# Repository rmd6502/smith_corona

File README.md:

smith_corona
============

Driver for Smith Corona typewriter

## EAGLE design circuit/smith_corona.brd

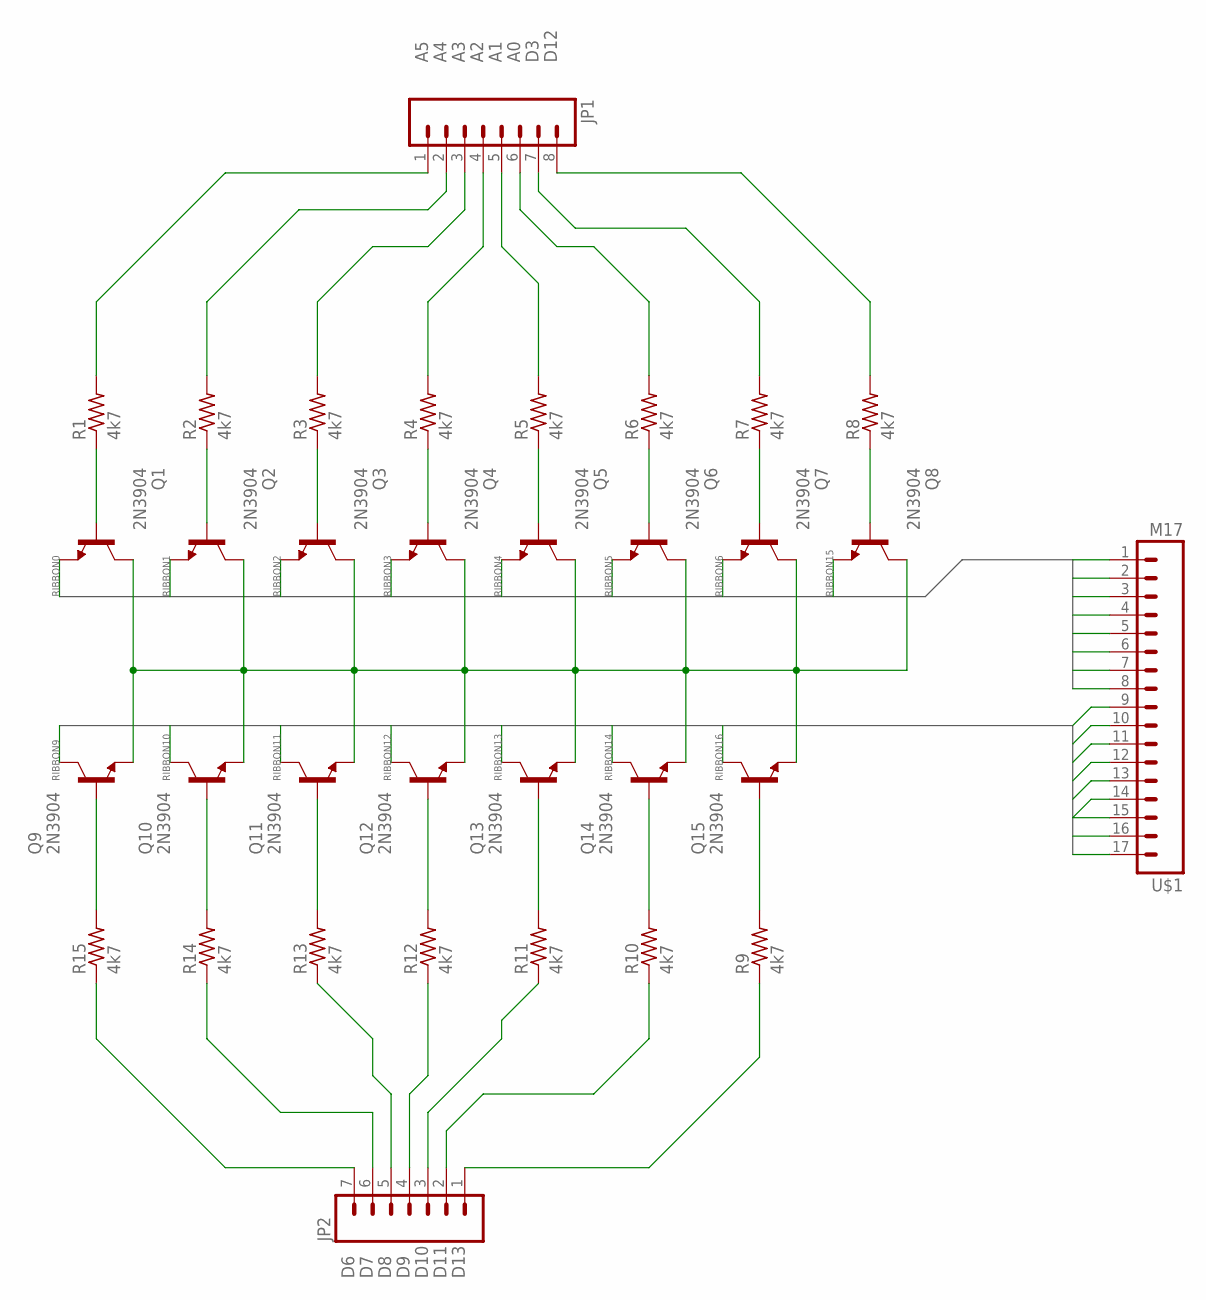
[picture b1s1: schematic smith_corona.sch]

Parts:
JP1: M08LONGPADS; 1X08_LONGPADS
JP2: M07LONGPADS; 1X07_LONGPADS
Q1, Q2, Q3, Q4, Q5, Q6, Q7, Q8, Q9, Q10, Q11, Q12, Q13, Q14, Q15: 2N3904; TO92
R1, R2, R3, R4, R5, R6, R7, R8, R9, R10, R11, R12, R13, R14, R15: 4k7; 0207/10
U$1: M17; 1X17

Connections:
A0: JP1.6, R6.2
A1: JP1.5, R5.2
A2: JP1.4, R4.2
A3: JP1.3, R3.2
A4: JP1.2, R2.2
A5: JP1.1, R1.2
D3: JP1.7, R7.2
D6: JP2.7, R15.1
D7: JP2.6, R14.1
D8: JP2.5, R13.1
D9: JP2.4, R12.1
D10: JP2.3, R11.1
D11: JP2.2, R10.1
D12: JP1.8, R8.2
D13: JP2.1, R9.1
unnamed: Q1.2 (B), R1.1
unnamed: Q2.2 (B), R2.1
unnamed: Q3.2 (B), R3.1
unnamed: Q4.2 (B), R4.1
unnamed: Q5.2 (B), R5.1
unnamed: Q6.2 (B), R6.1
unnamed: Q7.2 (B), R7.1
unnamed: Q8.2 (B), R8.1
unnamed: Q15.2 (B), R9.2
unnamed: Q14.2 (B), R10.2
unnamed: Q13.2 (B), R11.2
unnamed: Q12.2 (B), R12.2
unnamed: Q11.2 (B), R13.2
unnamed: Q10.2 (B), R14.2
unnamed: Q9.2 (B), R15.2
unnamed: Q1.1 (C), Q2.1 (C), Q3.1 (C), Q4.1 (C), Q5.1 (C), Q6.1 (C), Q7.1 (C), Q8.1 (C), Q9.3 (E), Q10.3 (E), Q11.3 (E), Q12.3 (E), Q13.3 (E), Q14.3 (E), Q15.3 (E)
RIBBON0: Q1.3 (E), U$1.1
RIBBON1: Q2.3 (E), U$1.2
RIBBON2: Q3.3 (E), U$1.3
RIBBON3: Q4.3 (E), U$1.4
RIBBON4: Q5.3 (E), U$1.5
RIBBON5: Q6.3 (E), U$1.6
RIBBON6: Q7.3 (E), U$1.7
RIBBON7: U$1.8
RIBBON8: U$1.9
RIBBON9: Q9.1 (C), U$1.10
RIBBON10: Q10.1 (C), U$1.11
RIBBON11: Q11.1 (C), U$1.12
RIBBON12: Q12.1 (C), U$1.13
RIBBON13: Q13.1 (C), U$1.14
RIBBON14: Q14.1 (C), U$1.15
RIBBON15: Q8.3 (E), U$1.16
RIBBON16: Q15.1 (C), U$1.17

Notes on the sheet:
D12
D10
D11
D13

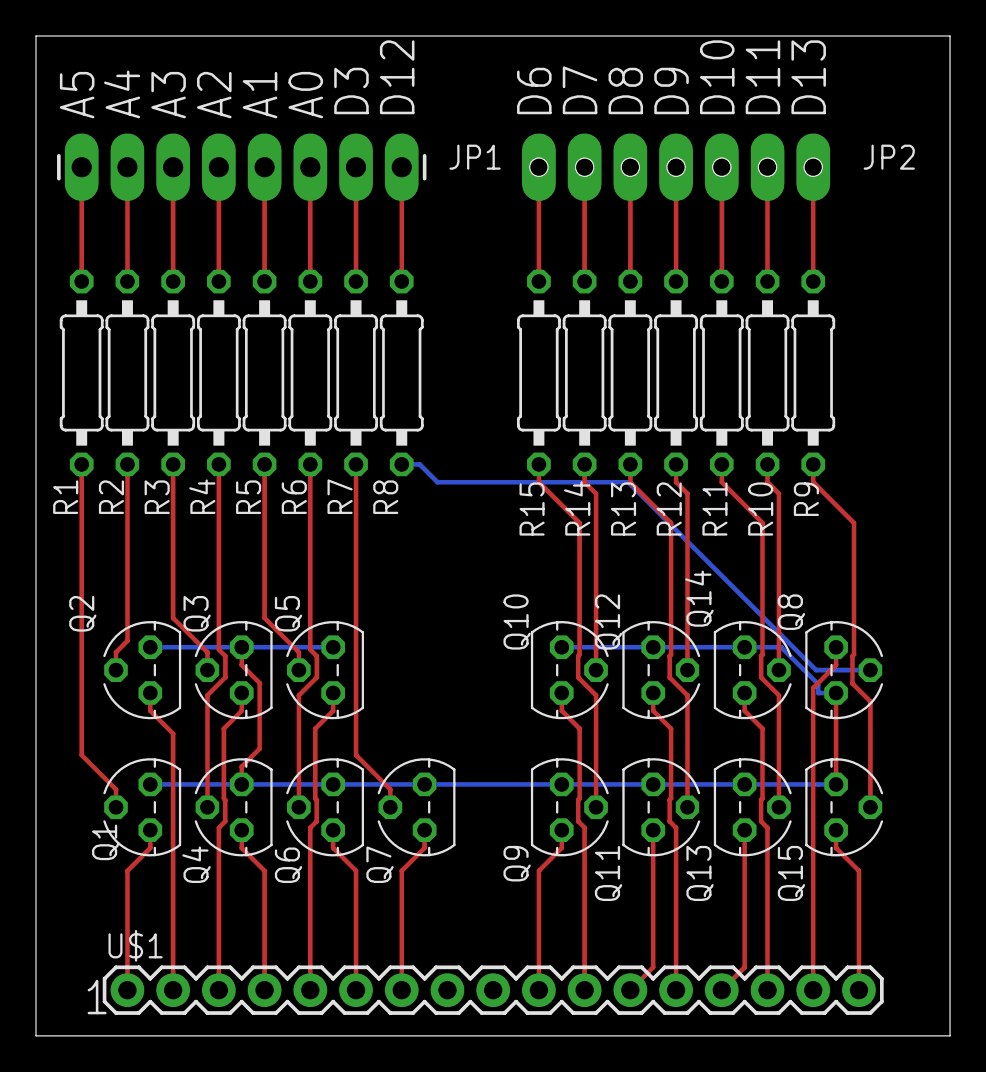
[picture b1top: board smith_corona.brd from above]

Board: 2 copper layers, 50.8 x 55.5 mm, 33 parts (1 on the bottom side), 46 nets.

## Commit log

2014-03-08 initial
2014-03-09 latest
2014-03-09 more complete, but completely untested
2014-03-09 add pdf
2014-03-09 tweak some wires
2014-03-10 fix board more

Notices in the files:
parts and their libraries:
SparkFun: Licensing: CC v3.0 Share-Alike You are welcome to use this library for commercial purposes.
